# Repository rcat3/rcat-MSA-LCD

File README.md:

# DroneLab

This project features firmware and 3D printable housings for small round Waveshare touch displays.  While primarily intended to screw into the voice port on the front of an MSA Millennium gas mask, this ecosystem was designed to be flexible.  The immediate audience will be "latex drones" desiring slick high-tech accessories for their gas mask.  Though cosplayers and other costume designers might find the project suits their needs as well.  

What started as a simple application to display images on Waveshare displays has grown into a small platform.  The same firmware runs on several displays, and the bigger ones can also light up with your voice, change it, play sound, control Lovense devices and be run from a phone.

*The housings, to scale.  From left: the 1.28" housing (RP2040 or RP2350), the 1.46" simple housing, the 1.46" speaker housing, and the 1.75" speaker housing.*

## What it does

You swipe up and down between features, and left and right between each feature's pages (see [Using the Display](docs/using-the-display.md)).

- **[Images](docs/features/images.md)**: still images and animated GIFs, built into the firmware or from an SD card.
- **[KITT and the Voice Ring](docs/features/kitt-and-voice-ring.md)**: red bars like KITT's voice box, or a glowing ring around the edge, that light up as you talk.
- **[Voice Effects](docs/features/voice-effects.md)**: changes your voice on the board itself, from a natural female voice to a robot or a Dalek.
- **[Voice Lab](docs/features/voice-lab.md)**: streams the microphone to a computer, for trying out voice effects.
- **[Sound](docs/features/sound.md)**: plays WAV, MP3 and FLAC files from the SD card.
- **[Lovense](docs/features/lovense.md)**: controls up to three Lovense devices over Bluetooth, with patterns and reactions to your voice and movement.
- **[Level](docs/features/level.md)**: a spirit level, for lining the display up on the mask.
- **[Terminal](docs/features/terminal.md)**: shows text typed on a phone, like an old green-screen terminal.
- **[Phone Remote](docs/features/phone-remote.md)**: runs the whole display from a phone's web browser, over the display's own WiFi hotspot, with no app.
- **[Settings](docs/features/settings.md)**: brightness, rotation, what's shown at startup, and the battery voltage.

## Hardware

Four displays are supported, all made by Waveshare.  Each has a 3D printable housing in this repository that screws into the mask's voice port, and a build guide with everything needed to make it.

| | [RP2040-Touch-LCD-1.28](docs/hardware/waveshare_touch_lcd_1_28.md) | [RP2350-Touch-LCD-1.28](docs/hardware/waveshare_touch_lcd_1_28.md) | [ESP32-S3-Touch-LCD-1.46](docs/hardware/waveshare_esp32s3_touch_lcd_1_46.md) | [ESP32-S3-Touch-AMOLED-1.75](docs/hardware/waveshare_esp32s3_touch_amoled_1_75.md) |
|---|---|---|---|---|
| Screen | 1.28" round LCD, 240x240 | 1.28" round LCD, 240x240 | 1.46" round LCD, 412x412 | 1.75" round AMOLED, 466x466 |
| Processor | RP2040, 2 cores, 133 MHz | RP2350, 2 cores, 150 MHz | ESP32-S3, 2 cores, 240 MHz | ESP32-S3, 2 cores, 240 MHz |
| RAM | 264 kB | 520 kB | 512 kB + 8 MB PSRAM | 512 kB + 8 MB PSRAM |
| Microphone | | | One | Two |
| Speaker | | | Built in | Amplifier and speaker socket |
| Micro SD card | | | Yes | Yes |
| WiFi and Bluetooth LE | | | Yes | Yes |
| Accelerometer | Yes (not supported yet) | Yes (not supported yet) | Yes | Yes |
| Battery charging | 1 A | 1 A | Up to 2 A, power button | 300 mA, power button |
| Status | Works | Works | Works | Firmware and housing new, not yet tried |

Which features each one runs:

| Feature | RP2040 1.28" | RP2350 1.28" | ESP32-S3 1.46" | ESP32-S3 1.75" |
|---|:-:|:-:|:-:|:-:|
| [Images](docs/features/images.md) | Yes | Yes | Yes | Yes |
| [Full screen animated GIFs](docs/features/images.md#animated-gif-memory-use) | | Yes | From the SD card | From the SD card |
| [Images from the SD card](docs/features/images.md#images-on-the-sd-card) | | | Yes | Yes |
| [KITT and the Voice Ring](docs/features/kitt-and-voice-ring.md) | | | Yes | Yes |
| [Voice Effects](docs/features/voice-effects.md) | | | Yes | Yes |
| [Voice Lab](docs/features/voice-lab.md) | | | Yes | Yes |
| [Sound](docs/features/sound.md) | | | Yes | Yes |
| [Lovense](docs/features/lovense.md) | | | Yes | Yes |
| [Level](docs/features/level.md) | | | Yes | Yes |
| [Terminal](docs/features/terminal.md) | | | Yes | Yes |
| [Phone Remote](docs/features/phone-remote.md) | | | Yes | Yes |
| [Settings](docs/features/settings.md) | Yes | Yes | Yes | Yes |

### Choosing one

| | |
|---|---|
|  | **[RP2040 or RP2350, 1.28"](docs/hardware/waveshare_touch_lcd_1_28.md)**: the simplest, smallest and cheapest build, for showing images.  Two printed parts and no screws, with the battery and a power switch inside, standing about 12 mm out of the mask.  Get the RP2350: it costs the same as the RP2040 and has room for full screen animated GIFs. |
|  | **[ESP32-S3, 1.46", simple housing](docs/hardware/waveshare_esp32s3_touch_lcd_1_46.md#the-simple-housing)**: every feature, in one printed part with no soldering.  The board's built-in speaker faces into the mask, so it's best for images, voice displays, Lovense control and the phone remote, rather than for sound. |
|  | **[ESP32-S3, 1.46", speaker housing](docs/hardware/waveshare_esp32s3_touch_lcd_1_46.md#the-speaker-housing)**: every feature, with two speakers facing out for sound and voice effects, a 2000 mAh battery and its own USB-C charging port.  The most involved build: two amplifier boards and a small adapter PCB to solder. |
|  | **[ESP32-S3, 1.75" AMOLED](docs/hardware/waveshare_esp32s3_touch_amoled_1_75.md)**: every feature on the biggest, sharpest screen, with true blacks, two microphones, a speaker below the display and a 2000 mAh battery.  The board has its own amplifier, so there's nothing to solder but the speaker's plug.  New: not yet tried on a real board. |

The housings' designs are in [`hardware/`](hardware/), in [OpenSCAD](https://openscad.org/), organized by board.

## How the software is put together

The application in `core/` is the same on every board.  It's written in C with the [LVGL](https://lvgl.io) graphics library, and reaches the hardware only through a small set of functions in [`core/include/hal.h`](core/include/hal.h), which each board implements with its own SDK: [pico-sdk](https://github.com/raspberrypi/pico-sdk) for the RP2040 and RP2350, and [ESP-IDF](https://docs.espressif.com/projects/esp-idf/en/v5.5.5/esp32s3/get-started/) for the ESP32-S3.

- **Features are modules.**  Each one is a single file, and can be switched on or off for a build.  A feature that needs hardware the board doesn't have, like a microphone or WiFi, hides itself.
- **Boards share what they can.**  Adding a display means adding its board folder, with its HAL and screen size, without copying the application around.  The ESP32 boards share everything that doesn't depend on the board.
- **One set of images for every screen.**  Images are converted for each board's screen size when the firmware is built, and the layout scales from 240x240, so the same files and pages work everywhere.

See [Developing](docs/development/README.md) for how it fits together, and how to add a feature or a board.

## Documentation

- **Building one:** pick a display above, then follow its build guide: [1.28"](docs/hardware/waveshare_touch_lcd_1_28.md), [1.46"](docs/hardware/waveshare_esp32s3_touch_lcd_1_46.md) or [1.75"](docs/hardware/waveshare_esp32s3_touch_amoled_1_75.md).  Each has the parts to buy, printing, wiring, putting it together, and building and flashing the firmware.
- **[Building the Firmware](docs/building-firmware.md):** getting the code, setting up pico-sdk or ESP-IDF, building, flashing, and choosing which features to build.
- **[Using the Display](docs/using-the-display.md):** finding your way around, and turning it on and off.
- **[Features](docs/features/README.md):** each feature in detail, with what it needs.
- **[Developing](docs/development/README.md):** how it's put together, [adding a feature](docs/development/adding-a-feature.md), [the hardware abstraction layer](docs/development/hardware-abstraction.md) and [adding a board](docs/development/adding-a-board.md).
- **[Hardware designs](hardware/):** the housings, PCBs and cases, and how they're organized.

## Acknowledgement

The first housing for the 1.28" display was the [RP2040-LCD-1.28-MSA](https://www.printables.com/model/538771-rp2040-lcd-128-msa) model by whyrlpool.  Their voice port thread has been reused by every housing in this project.  The housings are under their own Creative Commons licenses, which are described in [`hardware/`](hardware/README.md#licenses).

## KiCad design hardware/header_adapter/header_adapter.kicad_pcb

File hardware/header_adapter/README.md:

# J9 header adapter

A small PCB that solders onto the 2x10, 1.27 mm pin header (J9) on the back of the Waveshare ESP32-S3-Touch-LCD-1.46. It replaces the ribbon cable in the speaker housing (`hardware/enclosure/msa_1_46_speaker_housing.scad`). All the wiring to the back of the housing plugs into one 10-pin JST SH socket on it. To take the board out for a firmware update, you unplug that socket and the battery, and nothing has to be cut or desoldered.

**Status: not built yet.**  The layout passes KiCad's design rules check. It hasn't been fitted.

The first version (in the commit that added this folder) had the header's two rows swapped, a mirror image of the real header, so every pad sat on the other pin of its pair.  Don't fit a board from those Gerbers: it would connect the USB 5V to the battery.  This version has pin 1's row along the edge, next to the socket, and was checked pin by pin against the board's silkscreen.

## Files

- `header_adapter.kicad_pcb`, `header_adapter.kicad_pro` - the KiCad 6 board. There's no schematic, since the board is small enough to read straight off the layout.  The pinout is below.
- `fab/header_adapter_gerbers.zip` - Gerbers and drill files, ready to upload to a board house.

## Ordering

- 2 layers, 1.6 mm thick, 1 oz copper.  Any finish and any colour.
- The board is about 11 x 16 mm.
- The smallest hole is 0.3 mm and the smallest track is 0.2 mm, which every common board house can make.

## Parts

| Ref | Part | Notes |
|---|---|---|
| J2 | JST SM10B-SRSS-TB | 10-pin SH (1.0 mm) side-entry socket |
| R1 | 10k, 0603 | Pull-down on the amplifiers' SD line, so they stay off while the board boots |
| - | JST SHR-10V-S housing and SH crimp leads | The mating plug.  Pre-crimped leads are much easier than crimping your own. |

## Socket pinout

Pin 1 of the socket is the end nearest pin 1 of the header.

| SH pin | Signal | J9 pin | Wire it to |
|---|---|---|---|
| 1 | GND | 3, 4, 12 | USB-C breakout GND |
| 2 | BAT | 2 | Amplifier Vin, then on to the other amplifier |
| 3 | USB_5V | 1 | USB-C breakout 5V |
| 4 | USB_5V | 1 | USB-C breakout 5V |
| 5 | GND | 3, 4, 12 | USB-C breakout GND |
| 6 | GND | 3, 4, 12 | Amplifier GND, then on to the other amplifier |
| 7 | SD (GPIO1) | 11 | Amplifier SD, then on to the other amplifier |
| 8 | DIN (GPIO3) | 13 | Amplifier DIN, then on to the other amplifier |
| 9 | LRC (GPIO13) | 20 | Amplifier LRC, then on to the other amplifier |
| 10 | BCLK (GPIO12) | 18 | Amplifier BCLK, then on to the other amplifier |

Each SH contact is rated for about 1 A, so the charging current shares two pins each way.  At the board's 2 A charge rate that's right at the rating.  If you'd like more margin, change R8 on the Waveshare board to about 190k, which charges at about 1 A.

Wire each amplifier signal to the first amplifier's pad. Then run a short wire from that pad to the same pad on the second amplifier, with two wires in the one hole.  Keep the 220 uF capacitor across Vin and GND at each amplifier.

## Assembly

1. Solder J2 and R1 to the adapter first, while it's flat.
2. Hold the Waveshare board with its back towards you and the USB-C port to the left.  The header then runs left to right, with pin 1 (the dot, labelled 5V) at its lower left.  The lower row (5V, G, DN, DP and so on) runs along the board's edge, and the upper row (BAT, G, SCL, SDA and so on) is towards the middle.  Fit the adapter over the pins with its square pad, marked "1", on pin 1.  The socket is then below the header, facing the board's edge (the micro SD side).
3. Push it down until it sits on the header's plastic.  The pins stand about 1.8 mm out of the adapter.
4. Solder all 20 pins, including the unused ones, for strength.
5. Check with a meter that USB_5V, BAT and GND aren't shorted to each other, and that SD reads about 10k to GND.

Before soldering, make sure nothing else on the back of the board, inside the adapter's outline, is as tall as the header's plastic.

## In the housing

`header_adapter = true` in `msa_1_46_speaker_housing.scad` (the default) cuts the back plate to the adapter's outline and adds a notch for the plug, so a body printed before the adapter needs reprinting.  The plug goes in from the space below the battery.  The adapter's 3D model is in `hardware/enclosure/msa_1_46_header_adapter.scad`.

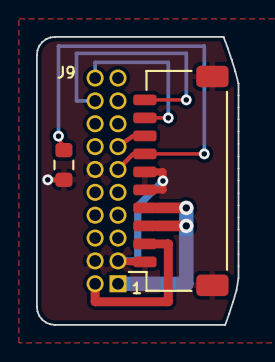
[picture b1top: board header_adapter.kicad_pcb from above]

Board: 2 copper layers, 11.2 x 16.0 mm, 3 parts (0 on the bottom side), 7 nets.

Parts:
J1: J9 2x10 1.27mm; Waveshare_J9_2x10_P1.27
J2: SM10B-SRSS-TB; JST_SH_SM10B-SRSS-TB_1x10-1MP_P1.00mm_Horizontal
R1: 10k; R_0603_1608Metric

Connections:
BAT: J1.2, J2.2
BCLK: J1.18, J2.10
DIN: J1.13, J2.8
GND: J1.3, J1.4, J1.12, J2.1, J2.5, J2.6, J2.MP, R1.1
LRC: J1.20, J2.9
SD: J1.11, J2.7, R1.2
USB_5V: J1.1, J2.3, J2.4

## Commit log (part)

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2025-03-03 Initial commit.
2025-03-08 Updated README.
2025-03-10 Testing animated GIFs. No luck.
2026-04-08 Working animated GIFs! They need to be small, though!
2026-04-09 Updated README markdown for animated GIFs.
2026-04-09 WIP: Setting up RP2350 version...
2026-04-09 WIP: Switching to common folders with different build configurations for different hardware.
2026-04-21 Added radar3 example GIF for RP2350 full screen demo.
